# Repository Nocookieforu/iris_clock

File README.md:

# Neopixel Clock

This project is mostly a copy of the
[Iris Clock](https://hackaday.io/project/1237-iris-clock) project that can
be found on Hackaday.io.

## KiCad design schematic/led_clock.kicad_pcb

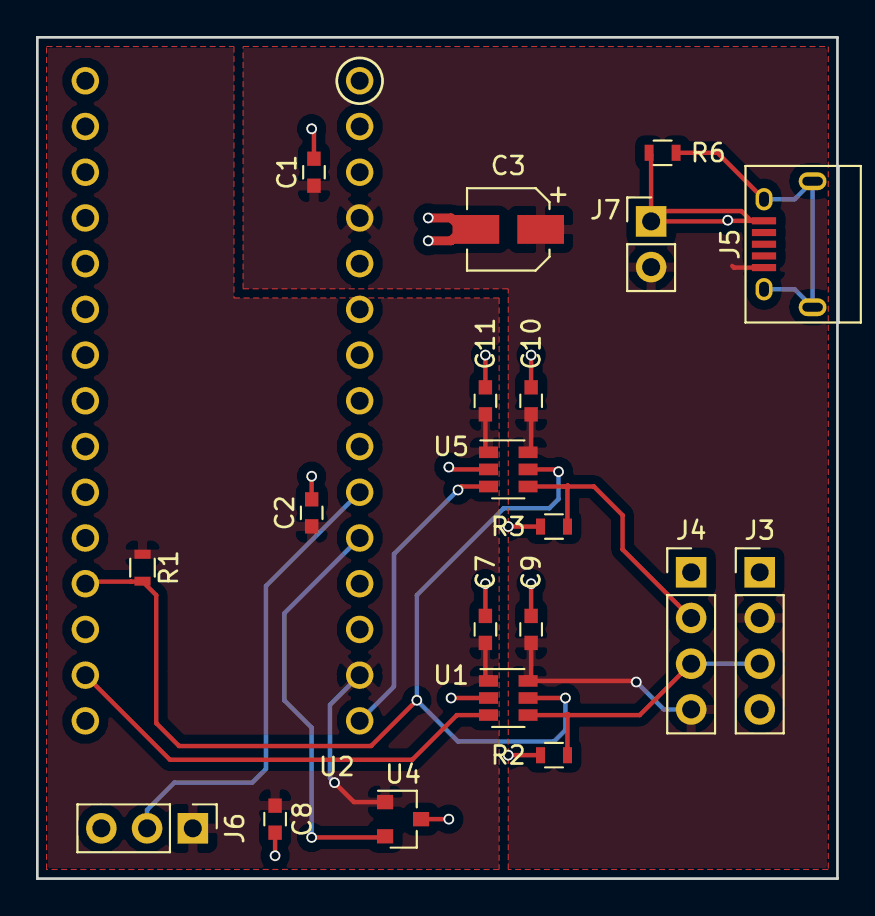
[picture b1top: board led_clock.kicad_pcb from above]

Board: 2 copper layers, 44.4 x 46.7 mm, 21 parts (0 on the bottom side), 11 nets.

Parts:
C1, C2, C7, C8, C9, C10, C11: 0.1u; C_0603
C3: 100u; CP_Elec_4x5.8
J3, J4: CONN_01X04; Pin_Header_Straight_1x04_Pitch2.54mm
J5: USB_OTG; USB_Micro-B
J6: CONN_01X03; Pin_Header_Straight_1x03_Pitch2.54mm
J7: CONN_01X02; Pin_Header_Straight_1x02_Pitch2.54mm
R1, R2, R3, R6: 10K; R_0603
U1, U5: SN74LVC1T45; SOT-23-6
U2: Nucleo32
U4: MCP9701; SOT-23

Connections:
+3V3: C2.1, C7.1, C8.1, C11.1, J6.1, R1.1, U1.1, U2.14, U4.1, U5.1
+5V: C1.1, C3.1, C9.1, C10.1, J3.2, J4.4, J5.1, J7.2, U1.6, U2.4, U5.6
DS_CLK: J4.2, R3.1, U5.4
DS_DAT: J3.3, J4.3, R2.1, U1.4
GND: C1.2, C2.2, C3.2, C7.2, C8.2, C9.2, C10.2, C11.2, J3.1, J4.1, J5.5, J6.3, J7.1, R2.2, R3.2, R6.2, U1.2, U2.2, U2.19, U4.3, U5.2
LUX: J6.2, U2.10
unnamed: J5.6, R6.1
PIX_CLK: U2.15, U5.3
PIX_DAT: U1.3, U2.29
PIX_DIR: R1.2, U1.5, U2.27, U5.5
TEMP: U2.11, U4.2

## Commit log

2017-07-26 Add README
2017-07-26 Copy parts of strandtest Arduino sketch
2017-07-26 Add method to show time
2017-07-26 Add hot color scheme to LEDs
2017-07-28 Add button debounce and brightness setting
2017-07-28 Use blue and green for better color mixing
2017-07-28 Read light value from analog sensor
2017-07-28 Implement exponential smoothing for light sensor
2017-07-28 Fix indentation
2017-07-28 Fix errors
2017-07-30 Create color editing functions for rgb and hsv
2017-07-30 Print test colors
2017-07-30 Switch colors using button
2017-07-30 Update color mixing to factor valueof both colors
2017-07-30 Mix colors all across strip for testing
2017-08-05 Create KiCAD project
2017-08-06 Set up basic schematic layout
2017-08-06 Add sensors to schematic
2017-10-11 Update schematic
2018-01-31 Rev 1.0 of circuit boards
2018-02-14 Create schematic images
2018-02-14 Add STM32CubeMX project
2018-02-14 First working version of firmware
2018-02-15 Update pinouts and set up rainbow
